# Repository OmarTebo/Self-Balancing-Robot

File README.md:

# Self-Balancing Robot (SBR)

A robust, feature-rich firmware for a two-wheeled self-balancing robot running on ESP32. Uses MPU6050 IMU with Kalman filtering, PID control, and supports both serial and BLE interfaces for telemetry and parameter tuning.

---

## Features

- **IMU Integration**: MPU6050 with Kalman filter fusion for stable angle estimation
- **PID Control**: Continuous-time PID controller with roll-axis balancing
- **Calibration Persistence**: NVS-stored calibration data with integrity checks
- **Test Mode**: Safe development mode with self-checks (motors disabled)
- **Multiple Interfaces**: Serial commands and BLE for remote control
- **Fixed-Timestep Loop**: 200Hz control loop with catch-up mechanism
- **Unit Tests**: Comprehensive test suite (34 tests) for algorithm verification
- **Development Tools**: Python utilities for telemetry plotting and PID tuning

---

## Hardware Requirements

- **MCU**: ESP32 (NodeMCU-32S or `esp32dev` board recommended)
- **IMU**: MPU6050 via I²C (SDA/SCL configurable in `Config.h`)
- **Motors**: Two NEMA stepper motors with A4988 drivers
- **Power**: Separate motor VMOT and logic 3.3V (common ground)
- **Optional**: LED matrix display (MAX7219) for status indication

Default pin mappings and constants are defined in `include/Config.h`.

---

## Quick Start

### Prerequisites

- [PlatformIO](https://platformio.org/) (VSCode extension or CLI)
- ESP32 USB driver installed
- Python 3.x (for development tools)

### Installation

```bash
# Clone repository
git clone https://github.com/OmarTebo/sbr.git
cd sbr

# Open in VSCode with PlatformIO extension, or use CLI:
pio run -t upload
```

### Initial Setup

1. **Configure hardware** (if needed): Edit `include/Config.h` for custom pin mappings
2. **Upload firmware**: `pio run -t upload`
3. **Open serial monitor**: `pio device monitor` (115200 baud)
4. **Calibrate IMU**: 
   - Place robot perfectly level
   - Send `CALIBRATE` via serial
   - Send `SAVE_CAL` to persist calibration

**⚠️ Safety**: Keep wheels off ground during initial tuning. Set A4988 current limits before enabling motors.

---

## Project Structure

```
sbr/
├── include/          # Public headers (API interfaces)
├── src/             # Implementation files
├── lib/MPU6050/     # MPU6050 driver and Kalman filter
├── test/            # Unit tests (Unity framework)
├── tools/           # Python development tools
│   ├── imu_telemetry_graph.py  # Real-time telemetry plotting
│   ├── pid_gui.py              # PID tuning GUI
│   └── dummy_imu_generator.py  # Test data generation
└── Documentation files:
    ├── DOCUMENTATION.md         # Technical API reference
    ├── DEVELOPER_GUIDE.md       # Development guide
    ├── PHASE_STATUS.md          # Implementation status
    └── TEST_FLOW_GUIDE.md       # Testing procedures
```

---

## Usage

### Serial Commands

```
# Calibration
CALIBRATE          # Run calibration (robot must be level!)
SAVE_CAL           # Save calibration to NVS
LOAD_CAL           # Load calibration from NVS
CLEAR_CAL          # Clear stored calibration
GET_CAL_INFO       # Show current calibration offsets

# System Info
GET_BOOT_TAG       # Show firmware version/tag
GET_STATUS         # Show system status
RUN_SELF_CHECKS    # Run diagnostic tests

# Test Mode
TEST_MODE_ON       # Enable test mode (disable motors)
TEST_MODE_OFF      # Disable test mode

# PID Control
GET PID            # Show current PID gains
SET PID <kp> <ki> <kd>  # Set PID gains
```

### BLE Interface

- **Service UUID**: `d1c6f3e0-9d3b-11ee-be56-0242ac120002`
- **Characteristics**: KP, KI, KD for PID parameter tuning
- **Device Name**: "SBR-Bot"

### Development Tools

```bash
# Real-time telemetry plotting
python tools/imu_telemetry_graph.py --port COM3

# Dummy data mode (algorithm verification)
python tools/imu_telemetry_graph.py --dummy

# PID tuning GUI
python tools/pid_gui.py
```

---

## PID Tuning

### Starting Values

- **Kp**: Start with `1.0` (proportional gain)
- **Ki**: Start with `0.0` (integral term - add later if needed)
- **Kd**: Start with `1.0` (derivative damping)

### Tuning Process

1. **Increase Kp** until robot responds to tilt
2. **Add Kd** to damp oscillations
3. **Add Ki** only if steady-state error persists (use sparingly)

### Units

- **Angles**: Degrees (°)
- **Angular velocity**: Degrees per second (°/s)
- **PID output**: Angular velocity in °/s (converted to motor steps/sec)

---

## Testing

### Unit Tests

```bash
# Run all unit tests
pio test -e esp32 --without-uploading

# Test results: 32/34 passing (94%)
# - PID tests: 10/10 ✅
# - Kalman tests: 8/10 ⚠️ (2 acceptable failures)
# - IMU tests: 14/14 ✅
```

### Hardware Testing

1. Run self-checks: `RUN_SELF_CHECKS`
2. Verify calibration: `GET_CAL_INFO`
3. Test motor directions (adjust flags in `Config.h` if needed)
4. Start with conservative PID gains
5. Monitor telemetry for stability

---

## Configuration

Key configuration options in `include/Config.h`:

- **Control Loop**: `CONTROL_LOOP_HZ` (default: 200Hz)
- **Motor Pins**: `LEFT_STEP_PIN`, `RIGHT_STEP_PIN`, etc.
- **Motor Direction**: `INVERT_LEFT_MOTOR`, `INVERT_RIGHT_MOTOR`, `SWAP_MOTORS`
- **PID Defaults**: `DEFAULT_PID_KP`, `DEFAULT_PID_KI`, `DEFAULT_PID_KD`
- **Test Mode**: `TEST_MODE_ENABLED` (compile-time flag)

---

## Documentation

- **[DOCUMENTATION.md](DOCUMENTATION.md)**: Complete API reference and technical details
- **[DEVELOPER_GUIDE.md](DEVELOPER_GUIDE.md)**: Comprehensive development guide (project state, workflow, planning)
- **[PHASE_STATUS.md](PHASE_STATUS.md)**: Implementation progress and roadmap
- **[TEST_FLOW_GUIDE.md](TEST_FLOW_GUIDE.md)**: Testing procedures and workflows

---

## Contributing

Contributions are welcome! Please:

1. Follow existing code style and structure
2. Add unit tests for new algorithms
3. Update documentation for API changes
4. Keep public headers minimal and well-documented
5. Document units clearly (degrees, deg/s, seconds)

---

## License

MIT License - see [LICENSE](LICENSE) file for details

---

## Acknowledgments

- MPU6050 driver and Kalman filter implementation
- AccelStepper library for motor control
- PlatformIO for build system
- Unity framework for unit testing

---

**Status**: Active development - See [PHASE_STATUS.md](PHASE_STATUS.md) for current progress

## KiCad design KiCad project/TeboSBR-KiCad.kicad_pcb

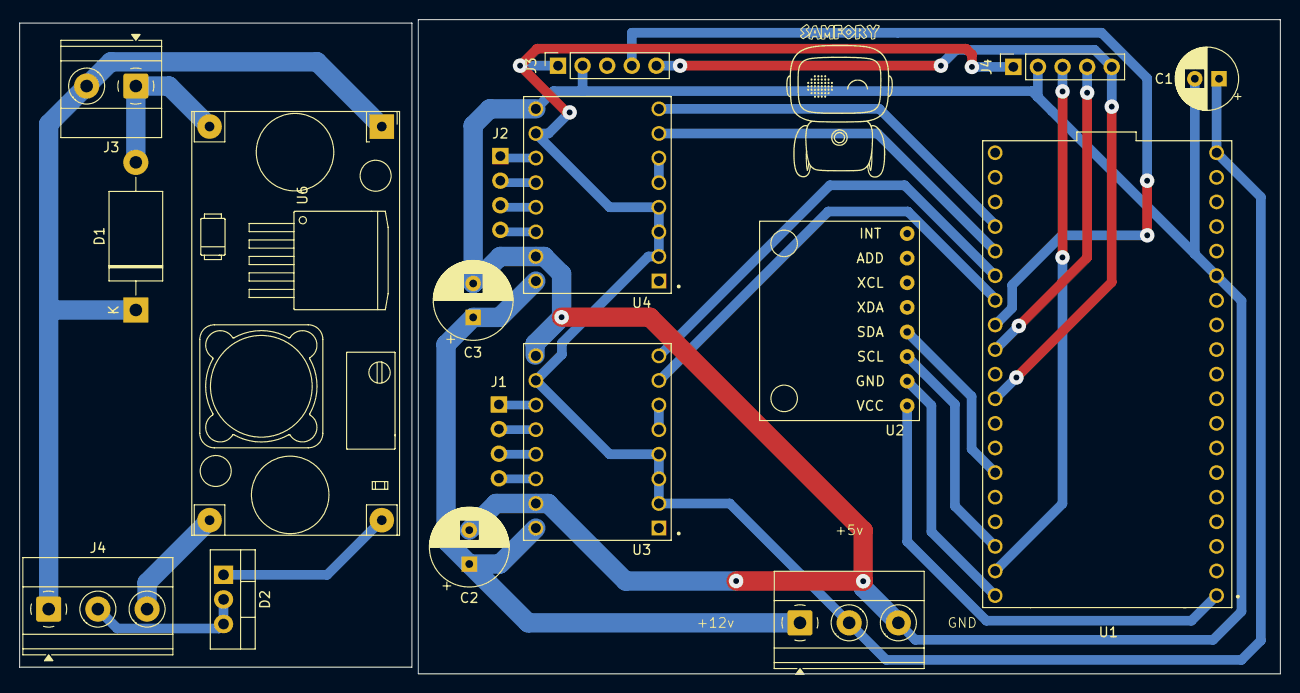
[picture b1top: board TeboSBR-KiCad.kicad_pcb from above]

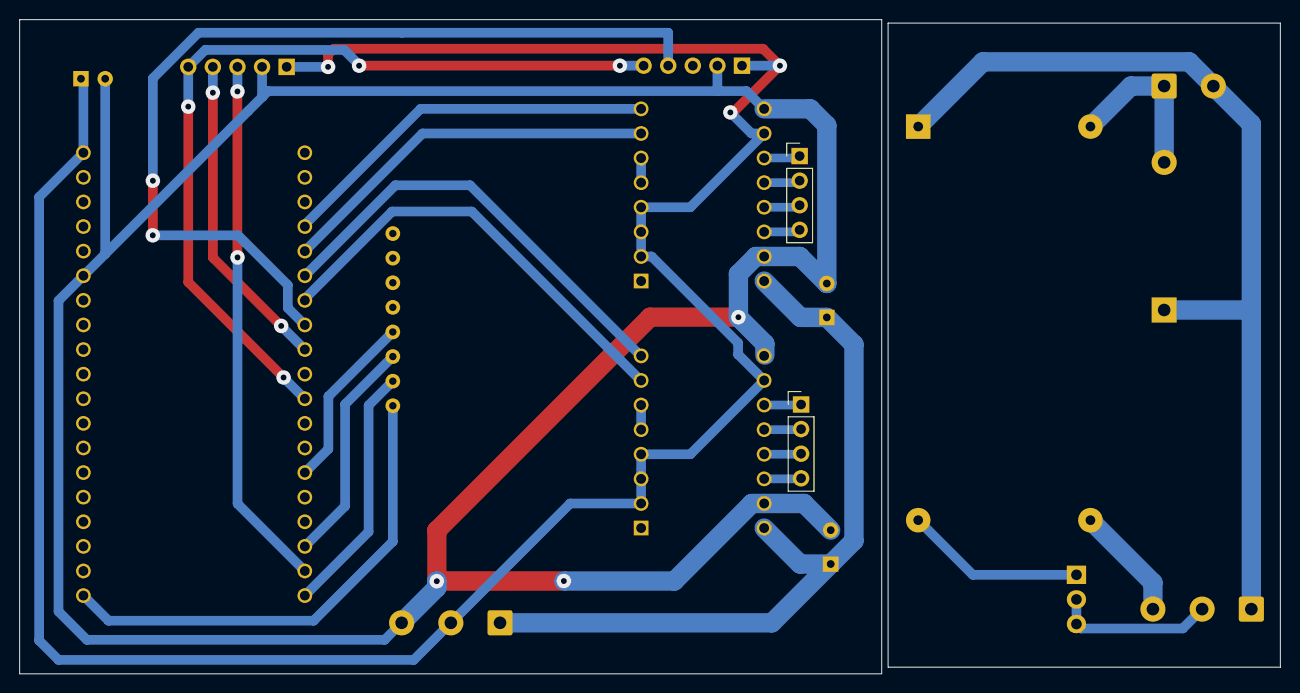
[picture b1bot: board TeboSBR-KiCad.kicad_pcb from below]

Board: 2 copper layers, 130.2 x 67.5 mm, 18 parts (2 on the bottom side), 25 nets.

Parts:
C1: 10uF; CP_Radial_D6.3mm_P2.50mm
C2, C3: 100uF; CP_Radial_D8.0mm_P3.50mm
D1: 1.5KE13A; D_DO-201AE_P15.24mm_Horizontal
D2: MBR3060CT; TO-220-3_Vertical
J1, J2: Conn_01x04; PinHeader_1x04_P2.54mm_Vertical
J3: Screw_Terminal_01x02; TerminalBlock_Phoenix_MKDS-1,5-2-5.08_1x02_P5.08mm_Horizont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
J3#2, J4: Conn_01x05; PinSocket_1x05_P2.54mm_Vertical
J4#2, J5: Screw_Terminal_01x03; TerminalBlock_Phoenix_MKDS-1,5-3-5.08_1x03_P5.08mm_Horizont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
SAMFORY: SAMFORY-FOOTPRINT
U1: ESP32-DEVKITC; NODEMCU-32S
U2: MPU6050; module_mpu6050
U3, U4: A4988_STEPPER_MOTOR_DRIVER_CARRIER; MODULE_A4988_STEPPER_MOTOR_DRIVER_CARRIER
U6: LM2596; DCDC_StepDown_LM2596

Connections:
+3.3V: U1.1 (3V3), U2.1 (VCC)
+5V: C1.1, D2.2 (K), D2.3 (K), J3#2.1, J4.1, J4#2.2, J5.2, U1.19 (EXT_5V), U3.2 (MS1), U3.3 (MS2), U3.4 (MS3), U3.10 (VDD), U4.2 (MS1), U4.3 (MS2), U4.4 (MS3), U4.10 (VDD)
+12V: C2.1, C3.1, D1.1 (A1), J3.2, J4#2.1, J5.1, U3.16 (VMOT), U4.16 (VMOT), U6.1 (Vin)
/CLK: J3#2.5, J4.5, U1.30 (IO18)
/CS1: J4.4, U1.28 (IO17)
/CS2: J3#2.4, U1.27 (IO16)
/DIN: J4.3, U1.37 (IO23)
/M1DIR: U1.25 (IO0), U3.8 (DIR)
/M1STEP: U1.26 (IO4), U3.7 (STEP)
/M2DIR: U1.23 (IO15), U4.8 (DIR)
/M2STEP: U1.24 (IO2), U4.7 (STEP)
/SCL: U1.36 (IO22), U2.3 (SCL)
/SDA: U1.33 (IO21), U2.4 (SDA)
GND: C1.2, C2.2, C3.2, D1.2 (A2), J3.1, J3#2.2, J4.2, J4#2.3, J5.3, U1.14 (GND1), U1.32 (GND2), U1.38 (GND3), U2.2 (GND), U3.9 (GND), U3.15 (GND__1), U4.9 (GND), U4.15 (GND__1), U6.2 (GND), U6.3 (GND)
unnamed: D2.1 (A), U6.4 (Vout)
unnamed: J1.1, U3.11 (1B)
unnamed: J1.2, U3.12 (1A)
unnamed: J1.3, U3.13 (2A)
unnamed: J1.4, U3.14 (2B)
unnamed: J2.1, U4.11 (1B)
unnamed: J2.2, U4.12 (1A)
unnamed: J2.3, U4.13 (2A)
unnamed: J2.4, U4.14 (2B)
unnamed: U3.5 (~RESET), U3.6 (~SLEEP)
unnamed: U4.5 (~RESET), U4.6 (~SLEEP)

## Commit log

2025-10-31 my new crunch addiction
2025-11-02 Apply sbr2_crunch_fixes.patch
2025-11-03 Cleanup: remove generated/test artifacts and temporary files
    Removed files:
    - __pycache__, compiled pyc files, diagram.json, pio-run.log, wokwi.toml
    - test scripts and temporary patches (sbr_tuner.py, sbr2_crunch_fixes.patch, main_performance_test.cpp.disabled)
    Purpose:
    - Keep repository clean of generated artifacts and local test files.
    - Added .gitignore entries to prevent these files from being re-added.
2025-11-28 Add LED matrix display support with animation
    - Add display GPIO pins to Config.h (DIN=23, CLK=18, CS1=17, CS2=16)
    - Create display.h and display.cpp for MD_MAX72XX LED matrix control
    - Implement animated smiley/sad face display on dual 8x8 matrices
    - Add MD_MAX72XX library dependency to platformio.ini
    - Integrate display setup and update calls into main loop
    - Display alternates between smiley and sad faces every second
2025-11-28 Integrate LED matrix display animation into BotController
    - Move display functionality from standalone display.cpp into BotController
    - Add MD_MAX72XX displayMatrix as private member in BotController
    - Initialize display in BotController::begin() with initial face patterns
    - Add throttled display update in BotController::update() (1 second intervals)
    - Implement updateDisplay() and displayBitmap() helper methods
    - Remove display calls from main.cpp - now fully handled by BotController
2025-12-06 Remove BNO055 dead code - beginBNO() declaration removed from IMU.h
2025-12-06 refactor: remove dead code and refactor display module
    Dead code removal:
    - Remove unused standalone compute() function from PIDController.h
    - Remove unused SerialCmdResult struct from SerialBridge.h
    - Remove unused beginMPU() declaration from IMU.h
    - Remove BNO055 support (beginBNO) - already committed separately
    Display module refactoring:
2025-12-06 docs: update documentation to reflect current codebase state
    Documentation updates:
    - Fix DEFAULT_PID_KD value (0.01f -> 1.0f) in examples
    - Add Display class documentation section
    - Update BotController section to reflect Display class usage
    - Add missing Config.h constants (CONTROL_LOOP_DT_S, motor signs, display pins, NVS keys)
    - Add missing implementation details (BLE UUIDs, motor defaults, MAX_CATCHUP_TICKS)
2025-12-06 refactor: rename motor pins to left/right and add invert/swap flags
    Motor pin renaming:
    - Rename PITCH_STEP_PIN -> LEFT_STEP_PIN (and related DIR/EN pins)
    - Rename ROLL_STEP_PIN -> RIGHT_STEP_PIN (and related DIR/EN pins)
    - Update HardwareMap.h with new pin aliases
    - Update BotController constructor to use new pin names
    Motor invert/swap configuration:
2025-12-06 feat: implement roll control for motor control
    Roll control implementation:
    - Add rollPid controller to BotController (primary controller for x-axis rotation)
    - Keep pitchPid for optional future use (if MPU6050 rotated)
    - Change motor control from pitch to roll (both motors rotate around x-axis)
    - Use imu.getRoll() and targetRoll for control instead of pitch
    - Update all PID operations to use rollPid
2025-12-06 docs: update documentation to reflect roll control implementation
    Documentation updates:
    - Update BotController section to document rollPid as primary controller
    - Update control flow to show roll PID computation
    - Update code examples to use roll control instead of pitch
    - Clarify that both motors respond to roll together
    - Note that pitchPid exists for optional future use
2025-12-06 feat: implement calibration persistence (Phase 1)
    Calibration persistence implementation:
    - Remove automatic calibration from IMU::begin() (prevents calibration while tilted)
    - Add explicit calibrateBlocking() method for user-initiated calibration
    - Add NVS persistence for calibration data (save/load/clear)
    - Add magic number and version checking for data integrity
    - Calibration loads automatically on boot if valid data exists
2025-12-06 feat: implement test mode (Phase 2) - Test mode for safe hardware verification without motor activation. Includes compile-time and runtime flags, self-check tests (IMU, I2C, motors, display, BLE, ser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
2025-12-06 feat: add matplotlib-based IMU telemetry grapher tool - Real-time plotting of PITCH, ROLL, YAW from serial telemetry - Optional expected values overlay from CSV file - Statistics display (mean, std d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
2025-12-06 feat: add dummy IMU data generator and algorithm extraction - Dummy IMU generator for testing without physical IMU hardware - Generates realistic acceleration and gyroscope data - Supports multiple p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
2025-12-06 fix: correct acceleration units in dummy generator and algorithm doc - Change acceleration from m/s to g-force units (1.0 = 1g) - Fix example calculation in algorithm extraction - Ensure consistency 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
2025-12-06 fix: add missing except block in load_expected_values - Fix SyntaxError: inner try block was missing except clause - Skip invalid CSV rows gracefully instead of crashing
2025-12-06 docs: add complete test flow guide - Comprehensive step-by-step testing guide from upload to validation - Covers all phases: setup, basic tests, dummy data, calibration, PID tuning - Includes trouble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
2025-12-06 feat: add dummy data mode to telemetry grapher for algorithm verification - Add --dummy flag to generate synthetic sensor data instead of reading serial - Add --pattern option (sine, step, tilt, stat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
2025-12-06 docs: add comprehensive phase status report - Track completion status of all 6 implementation phases - Show what's done, what's pending, and what's next - Include progress summary and recommendations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
2025-12-06 feat: implement Phase 4 unit tests - Complete unit test suite for PID, Kalman, and IMU algorithms - 34 comprehensive tests covering all critical functionality - PID tests: initialization, P/I/D terms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
2025-12-06 docs: update phase status - Phase 4 unit tests complete - 34 comprehensive tests for PID, Kalman, and IMU algorithms - Overall progress: 65% (3 phases complete)
2025-12-06 feat: implement Phase 4 unit tests (34 tests, 32 passing)
    - Created comprehensive unit test suite with Unity framework
    - 10 PID tests: all passing
    - 10 Kalman filter tests: 8 passing, 2 acceptable failures (filter works in practice)
    - 14 IMU algorithm tests: all passing
    - Fixed build configuration to exclude src/main.cpp from test builds
    - Disabled eye_test.cpp to prevent conflicts
2025-12-06 docs: reorganize documentation structure
    - Created professional README.md for public-facing documentation
    - Renamed ENGINEERING_OVERVIEW.md to DEVELOPER_GUIDE.md (personal reference)
    - Moved planning/session docs to docs/ folder for better organization
    - Fixed README.md project structure references
    - Removed duplicate ENGINEERING_OVERVIEW.md file
    Documentation now follows standard GitHub repo structure:
2025-12-17 Add runtime MPU6050 DLPF control with NVS persistence and serial commands
2025-12-17 Modified my testing flow guide to be more suitable for mates to copy-paste into serial
2025-12-20 Uploaded a copy of the last version of the PCB and its schematics with all used symbols and footprint libraries and more
